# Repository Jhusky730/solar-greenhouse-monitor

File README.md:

# Solar-Powered Environmental & Soil Monitor

An ultra-low-power ESP32-C3 environmental telemetry node with solar harvesting and deep sleep optimization.

## Project Info

This project is a monnitor for my greenhouse. It can measure:
- Soil Moisture
- Humidity
- Air Temperature

This will allow me to take better care of my plants, and hopefully achieve a higher yield.

I was inspired to create this project after seeing a video of a fully automated greenhouse, so I attempted to partially replicate it myself.

## Photos

## Implementation, Topology, and Assembly Reference

The custom PCB routes the ESP32-C3-WROOM-02U peripherals to external components using these net configurations:
* **USB Native Data (-)**: GPIO18 (IO18) at J4 (A7/B7) for native flashing.
* **USB Native Data (+)**: GPIO19 (IO19) at J4 (A6/B6) for native flashing.
* **I2C Data (SDA)**: GPIO2 (IO2) at J2 (Pin 3) for the SHT41 sensor port.
* **I2C Clock (SCL)**: GPIO10 (IO10) at J2 (Pin 4) as an overridden clock channel.
* **Analog Soil Signal**: GPIO1 (IO1) at J3 (Pin 3) via ADC1_CH1 for 12-bit sampling.
* **Boot Mode Strap**: GPIO9 (IO9) at R1/R3 pulled to 3V3 with a 10k Ohm resistor for flash boot.

The power system regulates input voltages to protect the 6V-maximum AP2112K regulator and the ESP32-C3. A 9V 600mA solar panel feeds a Waveshare Power Manager to charge a 3.7V 1200mAh LiPo battery and supply a stable 5V 3A rail to PCB terminal J1. Current flows through an SS14L Schottky diode (D1)—dropping voltage to ~4.6V—before entering the AP2112K regulator (U1) to distribute a stable 3.3V power plane.

Verify the board assembly matches this functional checklist before power activation:
1. **Polarization (C1)**: The printed stripe on the Kyocera AVX Tantalum capacitor must face away from Ground and connect to the +5V rail.
2. **Directional Flow (D1)**: The printed cathode stripe on the SS14L Schottky diode must point toward the filtering capacitors (C1/C2) and away from the J1 input block.
3. **USB Verification**: Connecting J4 via a data-rated Type-C cable must natively enumerate an *ESP32-C3 USB Serial/JTAG Controller* without manual driver installation.

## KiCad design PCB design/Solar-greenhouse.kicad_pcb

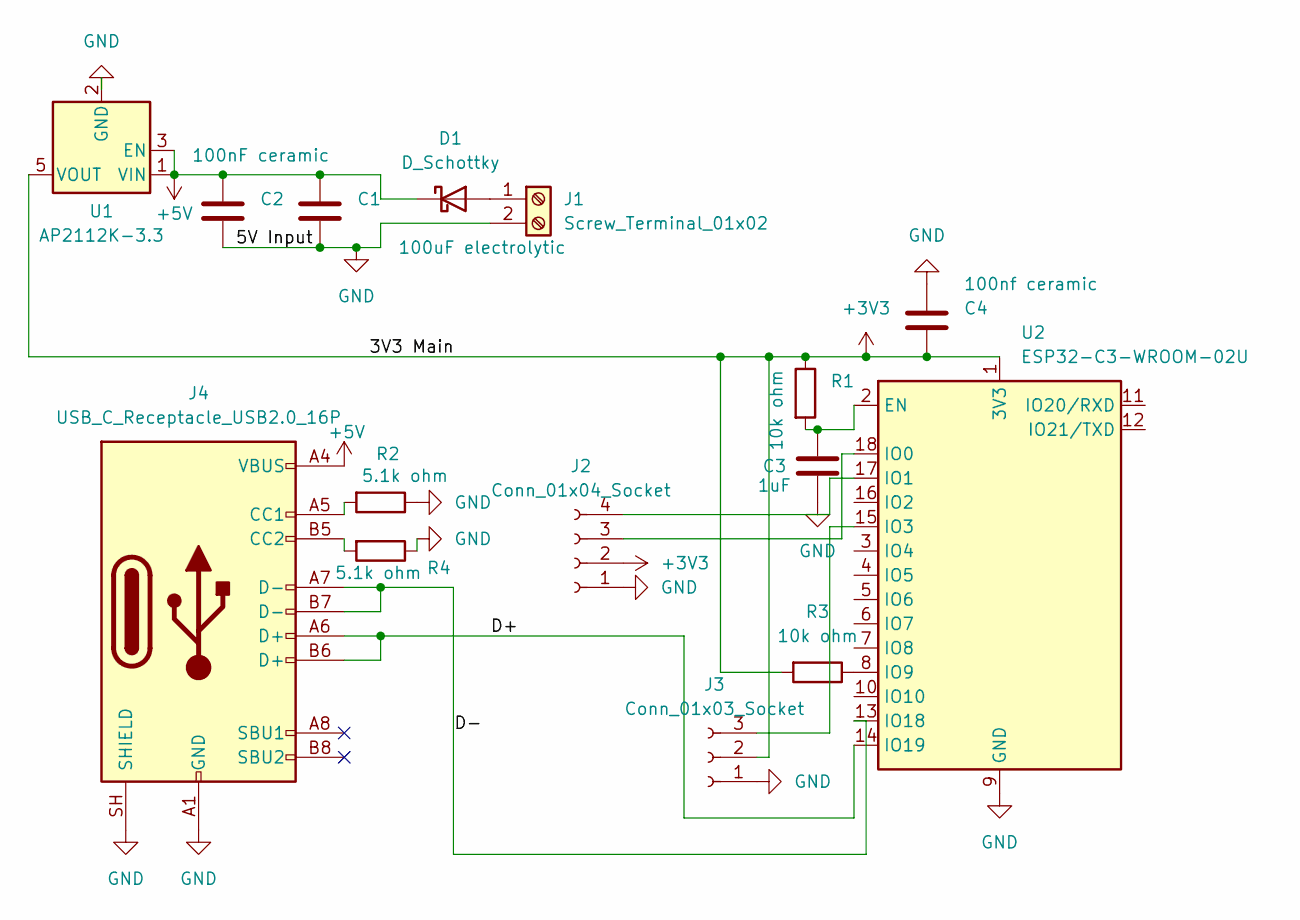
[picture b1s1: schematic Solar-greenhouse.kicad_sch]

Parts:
C1: 100uF electrolytic; CP_EIA-3528-21_Kemet-B_HandSolder
C2: 100nF ceramic; C_0805_2012Metric
C3: 1uF; C_0805_2012Metric
C4: 100nf ceramic; C_0805_2012Metric
D1: D_Schottky; D_SMA_Handsoldering
J1: Screw_Terminal_01x02; TerminalBlock_Phoenix_MKDS-1,5-2-5.08_1x02_P5.08mm_Horizont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
J2: Conn_01x04_Socket; JST_SH_SM04B-SRSS-TB_1x04-1MP_P1.00mm_Horizontal
J3: Conn_01x03_Socket; PinHeader_1x03_P2.54mm_Vertical
J4: USB_C_Receptacle_USB2.0_16P; USB_C_Receptacle_HRO_TYPE-C-31-M-12
R1, R3: 10k ohm; R_0805_2012Metric
R2, R4: 5.1k ohm; R_0805_2012Metric
U1: AP2112K-3.3; SOT-23-5
U2: ESP32-C3-WROOM-02U

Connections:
+3V3: C4.1, J2.2, J3.2, R1.1, R3.2, U1.5 (VOUT), U2.1 (3V3)
+5V: C1.1, C2.1, D1.1 (K), J4.A4 (VBUS), J4.A9 (VBUS), J4.B4 (VBUS), J4.B9 (VBUS), U1.1 (VIN), U1.3 (EN)
GND: C1.2, C2.2, C3.2, C4.2, J1.2, J2.1, J2.MP, J3.1, J4.A1 (GND), J4.A12 (GND), J4.B1 (GND), J4.B12 (GND), J4.SH (SHIELD), R2.1, R4.1, U1.2 (GND), U2.9 (GND), U2.19 (GND)
unnamed: D1.2 (A), J1.1
unnamed: J2.3, U2.18 (IO0)
unnamed: J2.4, U2.17 (IO1)
unnamed: J3.3, U2.15 (IO3)
unnamed: J4.A5 (CC1), R2.2
unnamed: J4.B5 (CC2), R4.2
unnamed: C3.1, R1.2, U2.2 (EN)
unnamed: R3.1, U2.8 (IO9)
unnamed: J4.A7 (D-), J4.B7 (D-), U2.13 (IO18)
unnamed: J4.A6 (D+), J4.B6 (D+), U2.14 (IO19)

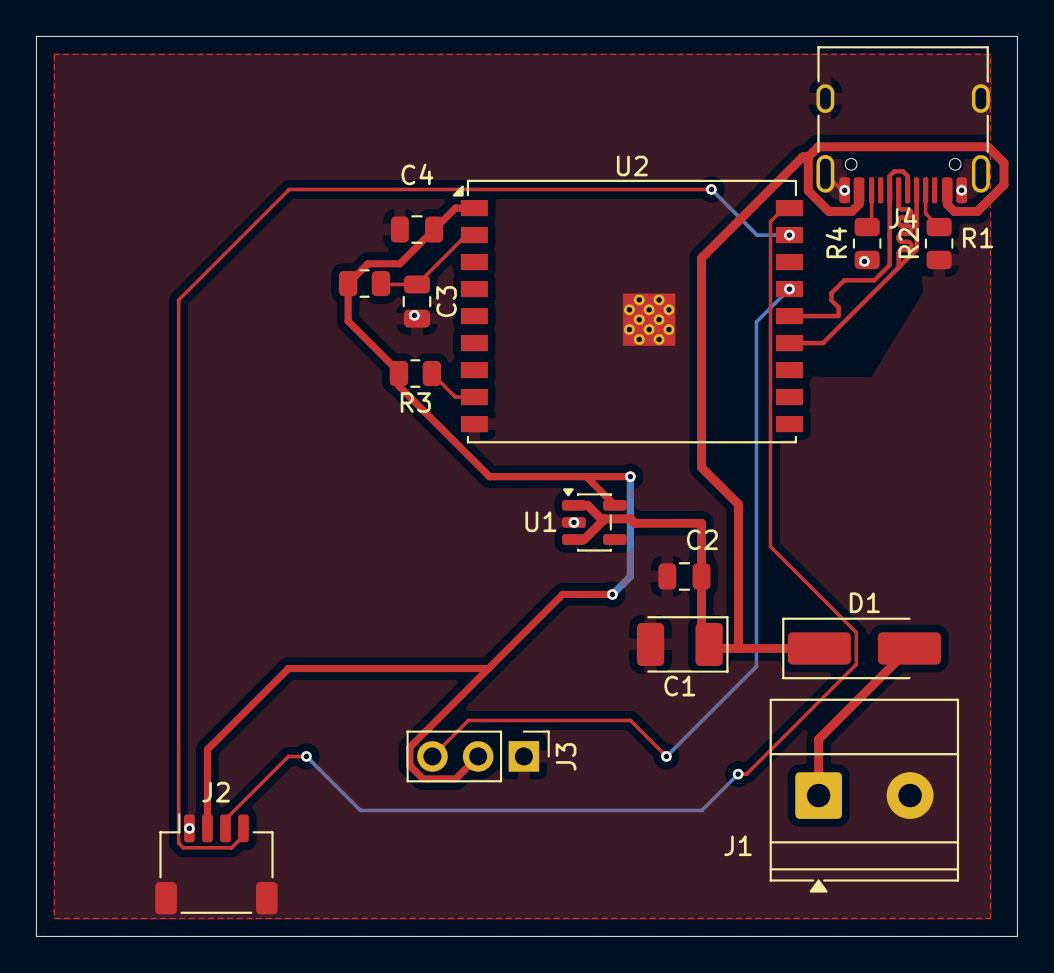
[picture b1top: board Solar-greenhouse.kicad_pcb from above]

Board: 2 copper layers, 54.5 x 50.0 mm, 15 parts (0 on the bottom side), 13 nets.

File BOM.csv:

Item,Quantity,Source,Part Number / Link,Manufacturer,MPN,Description,Package / Form Factor,Designator / Notes
1,1,LCSC,C2926676,ESPRESSIF,ESP32-C3-WROOM-02U-N4,2.4GHz ESP32-C3 Module (U.FL External Antenna),SMD-19P,U2
2,5,LCSC,C165948,Korean Hroparts Elec,TYPE-C-31-M-12,USB-C Receptacle 16 Position,SMD (16-Pin),J4
3,1,LCSC,C916292,MOLEX,1461530050,Flexible RF Antenna with U.FL/MHF Connector,Chassis Mount,ANT14
4,1,LCSC,C148107,Kyocera AVX,TPSB107M010R0400,100uF ±20% 10V Tantalum Capacitor 400mΩ,CASE-B-3528-21,C1 (Stripe AWAY from GND)
5,100,LCSC,C108451,Walsin,WR08X1002FTL,125mW 10kΩ Thick Film Resistor ±1%,0805,R1 R3 (Boot/Reset Pull-up)
6,100,LCSC,C84375,YAGEO,RC0805FR-075K1L,5.1kΩ 125mW Thick Film Resistor ±1%,0805,R2 R4 (USB-C CC Pull-down)
7,10,LCSC,C83055,Walsin,0805B104K500CT,100nF ±10% 50V Ceramic Capacitor X7R,0805,C2 C4
8,20,LCSC,C99915,Walsin,0805B105K500CT,1uF ±10% 50V Ceramic Capacitor X7R,0805,C3
9,10,LCSC,C125883,PANJIT,SS14L_R1_00001,Schottky Diode 40V 1A Surface Mount,SMA (DO-214AC),D1 (Stripe TOWARD Caps)
10,5,LCSC,C474952,Cixi Kefa Elec,KF128-5.08-2P-AA,2 Pos Wire to Board Terminal Block 5.08mm,Through Hole 5.08mm,J1 (Power Input)
11,5,LCSC,C22365427,MSKSEMI,AP2112K-3.3TRG1(MS),Linear Voltage Regulator IC Fixed 3.3V 600mA,SOT-23-5,U1
12,10,LCSC,C5445396,CJT,A2541WV-3P,Pin Header 3 Position 2.54mm Single Row,Through Hole 2.54mm,J3 (Moisture Expansion)
13,5,LCSC,C160404,JST,SM04B-SRSS-TB(LF)(SN),Connector Header 4 position 1mm Pitch 1A R/A,SMD Right Angle 1mm,J2 (Qwiic / STEMMA QT)
14,20,LCSC,C42393300,XFCN,XF7126,UL1007 22AWG Red Stranded Hookup Wire (100mm),Pre-cut Lead,Positive Power Paths
15,20,LCSC,C42393303,XFCN,XF7129,UL1007 22AWG Black Stranded Hookup Wire (100mm),Pre-cut Lead,Ground Return Loops
16,1,Pi Hut,https://thepihut.com,Adafruit,ADA4209,QT / Qwiic JST-SH 4-pin to Male Jumpers (150mm),Wire Harness,Connects J2 to SHT41 Breakout
17,1,Pi Hut,https://thepihut.com,PKCell,TTPH-LIPO-1200,3.7V LiPo Battery (JST-PH),Battery Pack,Plugs into Waveshare Manager
18,1,Pi Hut,https://thepihut.com,Waveshare,WS-16120,Power Manager Module (6V-24V),Pre-assembled Board,Steps down Panel to safe 5V/3A Output
19,1,Pi Hut,https://thepihut.com,Pi Hut,TTPH-SOLAR-9V,Solar Panel (9v 600mA),Chassis Panel,Powers Waveshare Manager Input
20,1,Pi Hut,https://thepihut.com,Pi Hut,TTPH-SOIL-MOIST,Capacitive Soil Moisture Sensor,Probe Module,Plugs into J3 via included Female cable
21,1,Pi Hut,https://thepihut.com,Sensirion,SHT41,"SHT41 Temp & Humidity Sensor, Breakout Board",Module,Plugs into J2 QT port via item 16
22,2,AliExpress,Moonlight electric,PG7-PG19-MIX,Nylon Cable Glands,"10Pcs Nylon Cable Glands IP68 (PG7/PG9 Assortment)",Hardware Pack,Enclosure Access Ports
23,1,AliExpress,FEITA Tools Store,FEITA-80W-KIT,Soldering Iron Kit,"80W LCD Digital Soldering Iron Kit (UK Plug)",Tooling Set,Assembly Tools
24,1,AliExpress,Wenzhou Xiangheng,IP67-ABS-BLK,Waterproof Box,"ABS Waterproof Box Housing Safe Case (Black)",Junction Box,Main Enclosure
